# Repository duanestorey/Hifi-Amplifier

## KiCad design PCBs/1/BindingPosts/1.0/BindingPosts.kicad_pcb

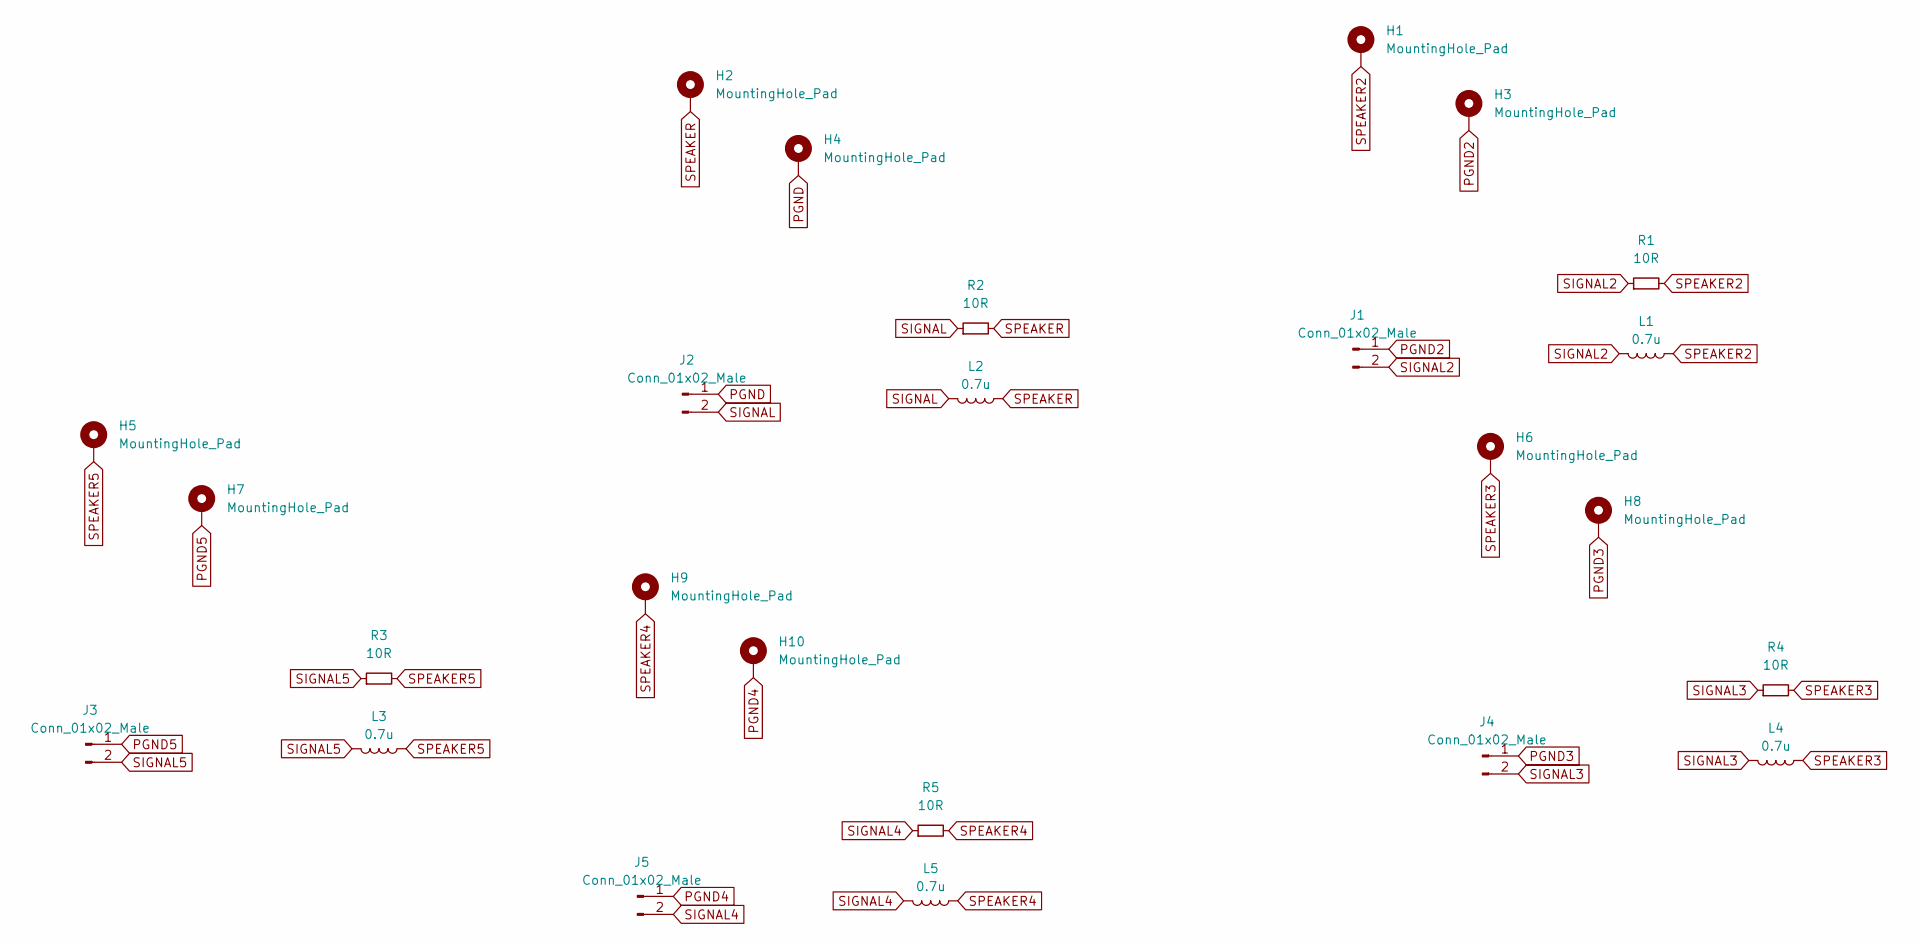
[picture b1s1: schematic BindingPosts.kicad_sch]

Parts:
H1, H2, H3, H4, H5, H6, H7, H8, H9, H10: MountingHole_Pad; MountingHole_4.3mm_M4_DIN965_Pad
J1, J2, J3, J4, J5: Conn_01x02_Male; JST_VH_B2P-VH-B_1x02_P3.96mm_Vertical
L1, L2, L3, L4, L5: 0.7u; L_Axial_L26.0mm_D10.0mm_P30.48mm_Horizontal_Fastron_77A
R1, R2, R3, R4, R5: 10R; R_Axial_Power_L25.0mm_W6.4mm_P27.94mm

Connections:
PGND: H4.1, J2.1
PGND2: H3.1, J1.1
PGND3: H8.1, J4.1
PGND4: H10.1, J5.1
PGND5: H7.1, J3.1
SIGNAL: J2.2, L2.2, R2.1
SIGNAL2: J1.2, L1.2, R1.1
SIGNAL3: J4.2, L4.2, R4.1
SIGNAL4: J5.2, L5.2, R5.1
SIGNAL5: J3.2, L3.2, R3.1
SPEAKER: H2.1, L2.1, R2.2
SPEAKER2: H1.1, L1.1, R1.2
SPEAKER3: H6.1, L4.1, R4.2
SPEAKER4: H9.1, L5.1, R5.2
SPEAKER5: H5.1, L3.1, R3.2

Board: 2 copper layers, 25 parts (0 on the bottom side), 15 nets, no tracks yet.

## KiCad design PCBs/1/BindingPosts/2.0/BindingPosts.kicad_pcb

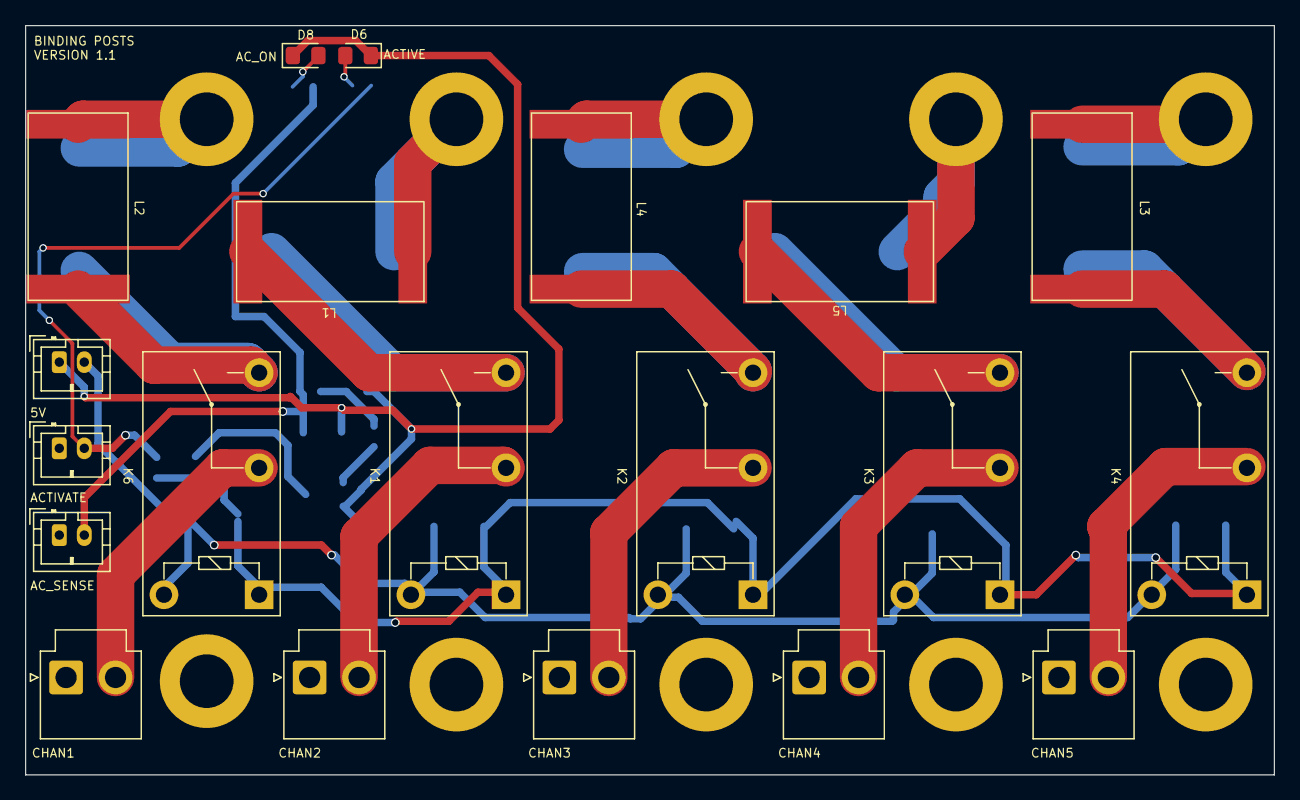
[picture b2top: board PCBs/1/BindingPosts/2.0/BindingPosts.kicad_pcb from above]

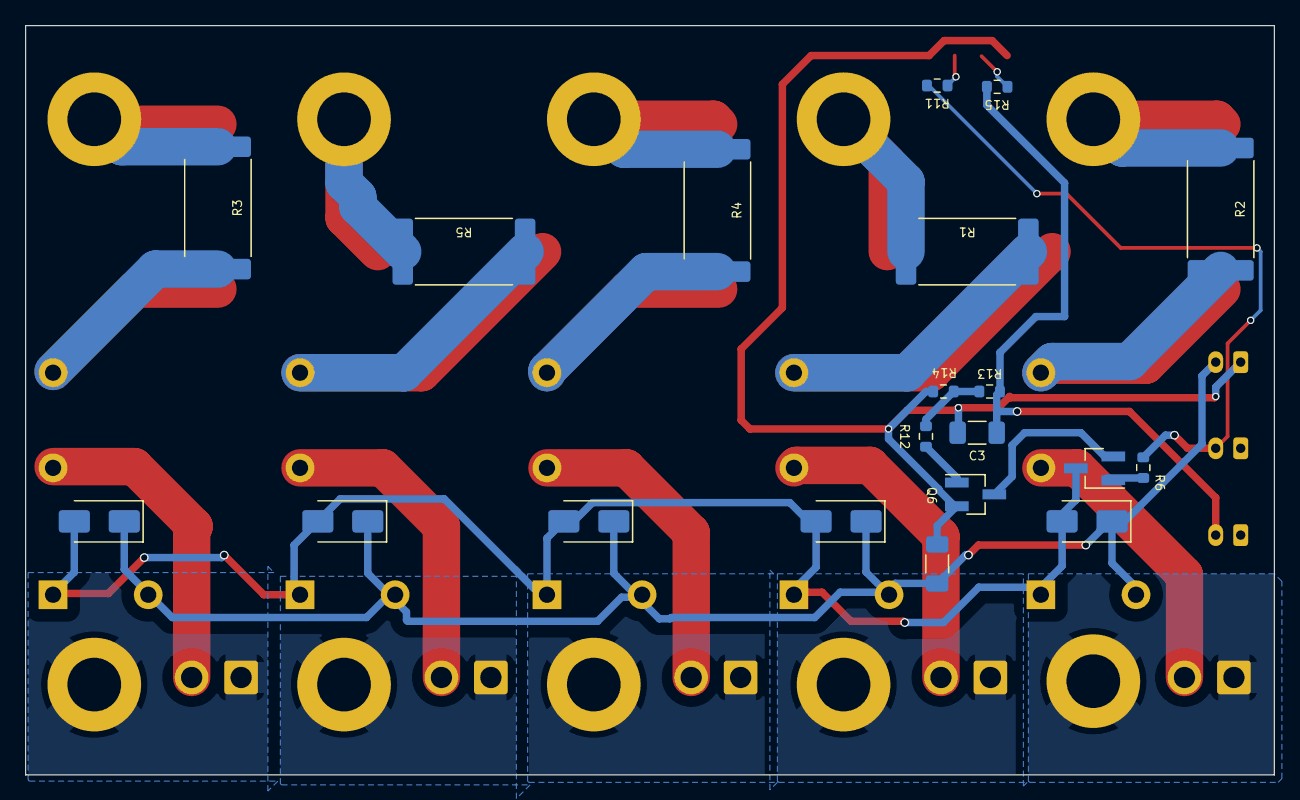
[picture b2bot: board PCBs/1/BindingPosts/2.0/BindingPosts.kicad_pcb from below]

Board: 2 copper layers, 100.0 x 60.0 mm, 50 parts (20 on the bottom side), 31 nets.

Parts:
C1: 10U; C_1206_3216Metric_Pad1.33x1.80mm_HandSolder
C3: 1U; C_1206_3216Metric_Pad1.33x1.80mm_HandSolder
D1, D2, D3, D4, D5: 1N4001; D_SMA
D6: RED; LED_0805_2012Metric_Pad1.15x1.40mm_HandSolder
D8: YELLOW; LED_0805_2012Metric_Pad1.15x1.40mm_HandSolder
H1, H2, H3, H4, H5, H6, H7, H8, H9, H10: MountingHole_Pad; MountingHole_4.3mm_M4_DIN965_Pad
J1, J2, J3, J4, J5: Conn_01x02_Male; JST_VH_B2P-VH-B_1x02_P3.96mm_Vertical
J6, J7, J8: Conn_01x02_Pin; JST_PH_B2B-PH-K_1x02_P2.00mm_Vertical
K1, K2, K3, K4, K6: G5Q-1; Relay_SPST_Omron-G5Q-1A
L1, L2, L4, L5: 0.5u; 929SQ-501JEC 500nh Air Core Inductor
L3: 538n; 929SQ-501JEC 500nh Air Core Inductor
Q1, Q6: 2SC1945; SOT-23_Handsoldering
R1, R2, R4, R5: 6.8R; R_4020_10251Metric_Pad1.65x5.30mm_HandSolder
R3: 7.5R; R_4020_10251Metric_Pad1.65x5.30mm_HandSolder
R6, R12: 820R; R_0603_1608Metric
R11: 360R; R_0603_1608Metric
R13: 20K; R_0603_1608Metric
R14: 10K; R_0603_1608Metric
R15: 430R; R_0603_1608Metric

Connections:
5V: C1.1, D1.1 (K), D2.1 (K), D3.1 (K), D4.1 (K), D5.1 (K), J6.2, K1.5, K2.5, K3.5, K4.5, K6.5
ACTIVATE: J7.2, R6.1, R11.2
AC_ACTIVE: R12.1, R13.1, R14.2
AC_SENSE: C3.1, J8.2, R13.2, R15.2
unnamed: D1.2 (A), D2.2 (A), D3.2 (A), D4.2 (A), D5.2 (A), K1.1, K2.1, K3.1, K4.1, K6.1, Q1.3 (C)
unnamed: D6.2 (A), R11.1
unnamed: D8.2 (A), R15.1
unnamed: Q1.1 (B), R6.2
unnamed: Q1.2 (E), Q6.3 (C)
unnamed: Q6.1 (B), R12.2
PGND: H4.1, J2.1
PGND2: H3.1, J1.1
PGND3: H8.1, J4.1
PGND4: H10.1, J5.1
PGND5: H7.1, J3.1
RELAY_GND: C1.2, C3.2, D6.1 (K), D8.1 (K), J6.1, Q6.2 (E), R14.1
SIGNAL1: J2.2, K6.2
SIGNAL1_OUT: K6.3, L2.2, R2.1
SIGNAL2: J1.2, K1.2
SIGNAL2_OUT: K1.3, L1.2, R1.1
SIGNAL3: J4.2, K2.2
SIGNAL3_OUT: K2.3, L4.2, R4.1
SIGNAL4: J5.2, K3.2
SIGNAL4_OUT: K3.3, L5.2, R5.1
SIGNAL5: J3.2, K4.2
SIGNAL5_OUT: K4.3, L3.2, R3.1
SPEAKER: H2.1, L2.1, R2.2
SPEAKER2: H1.1, L1.1, R1.2
SPEAKER3: H6.1, L4.1, R4.2
SPEAKER4: H9.1, L5.1, R5.2
SPEAKER5: H5.1, L3.1, R3.2

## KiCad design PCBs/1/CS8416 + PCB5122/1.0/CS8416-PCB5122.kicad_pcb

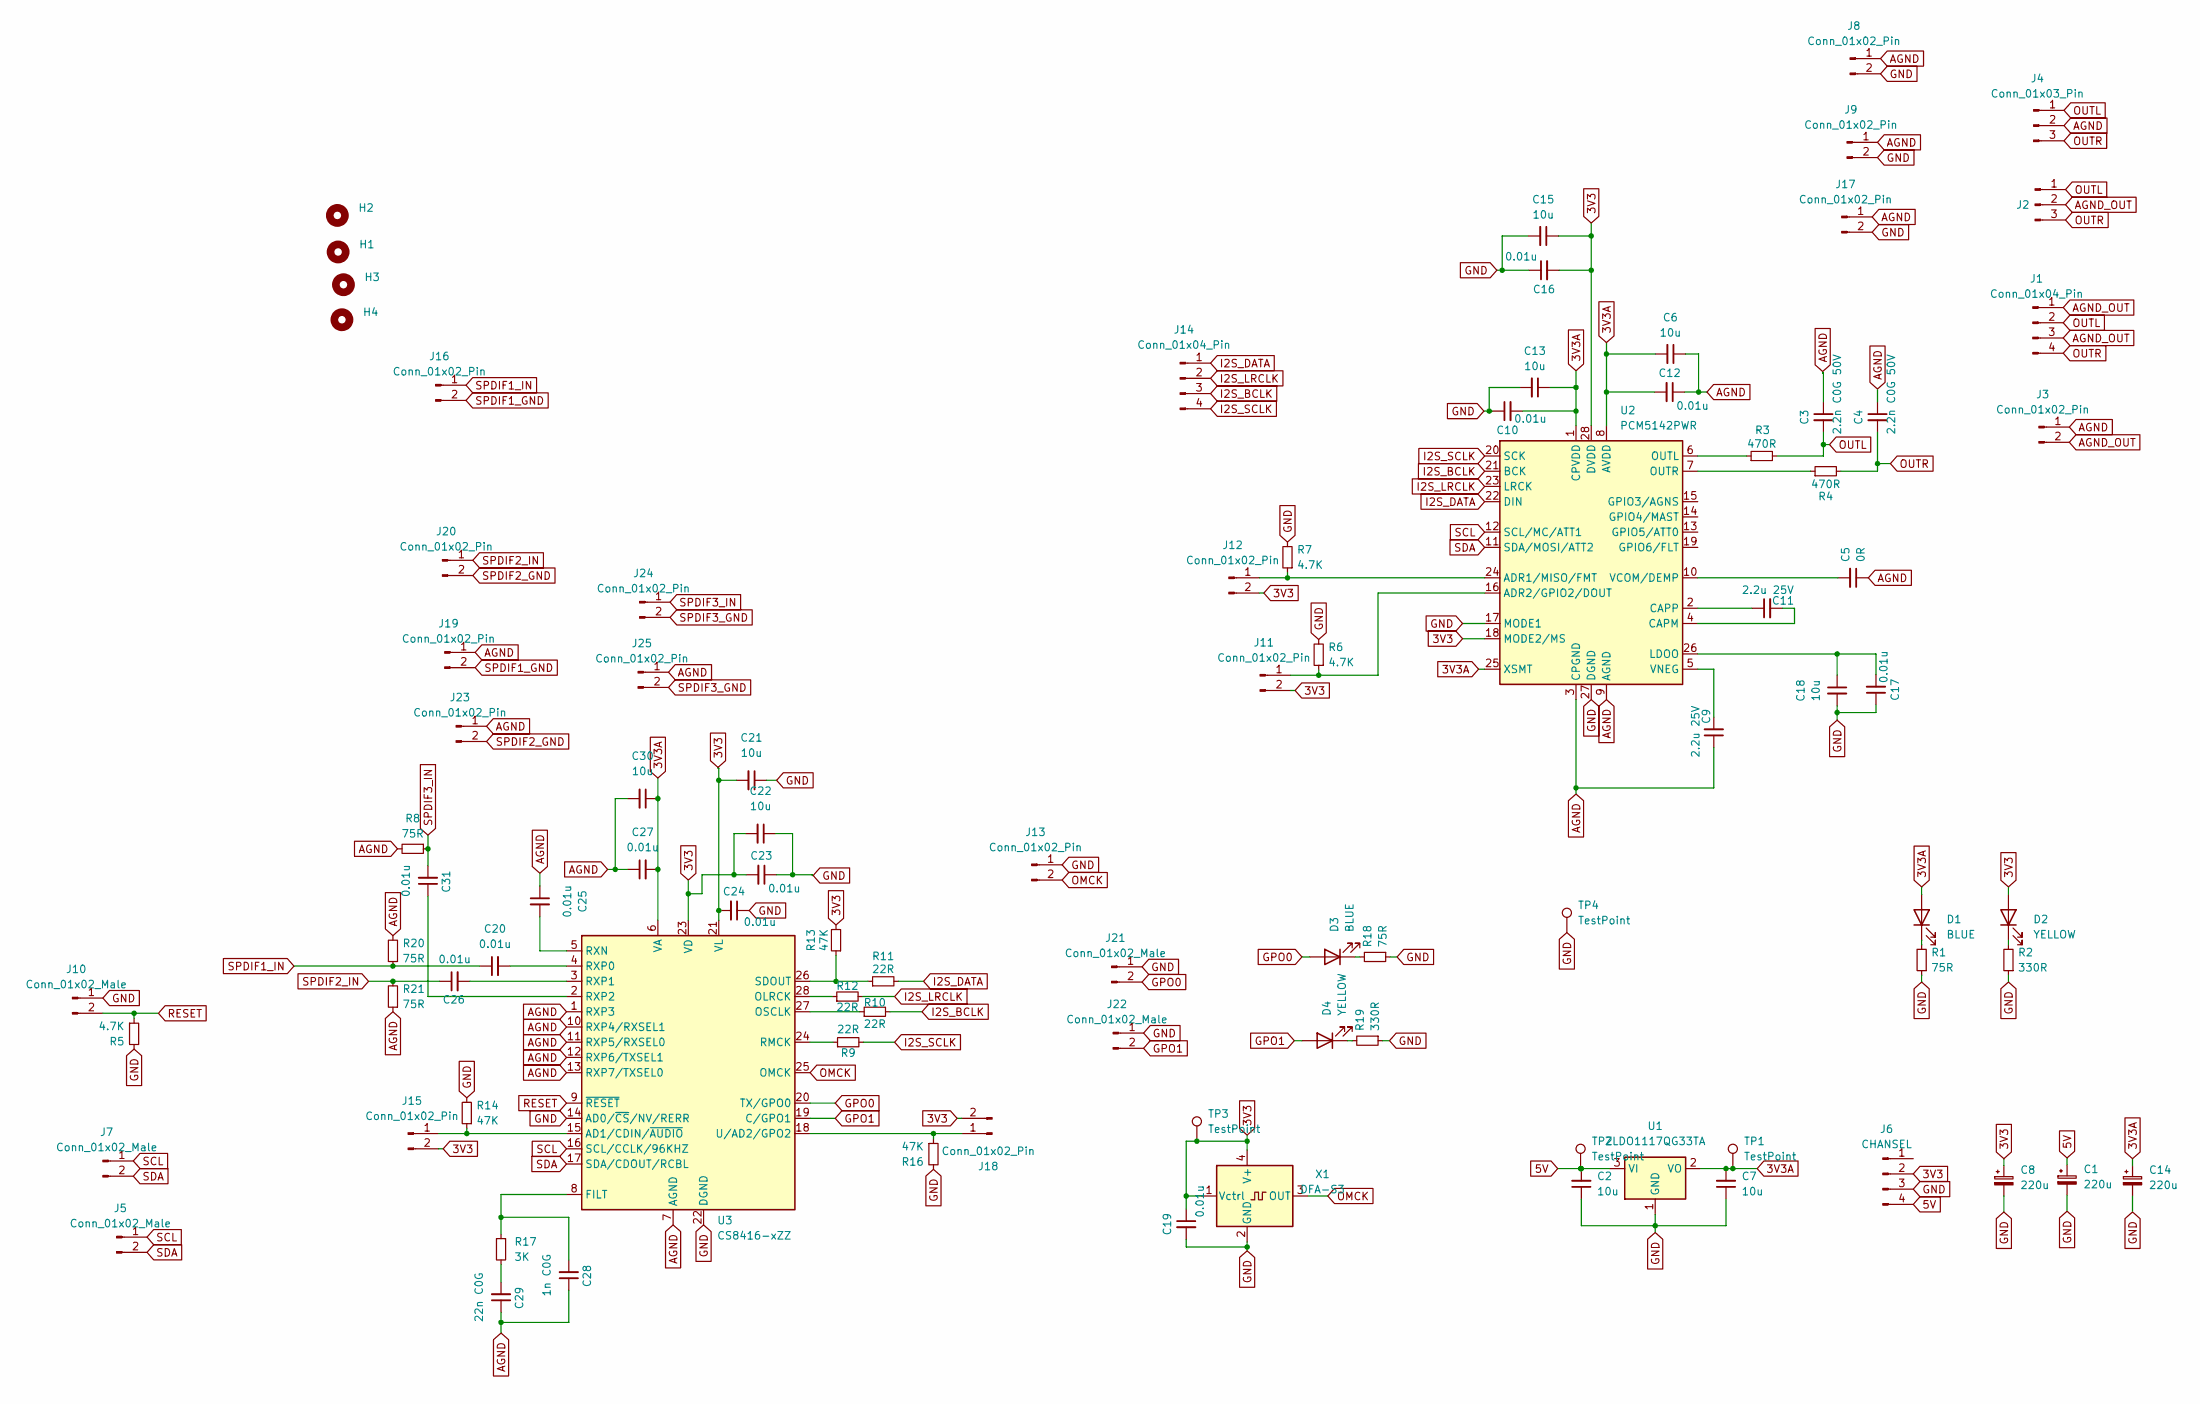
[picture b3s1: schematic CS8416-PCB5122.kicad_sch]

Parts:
C1, C8, C14: 220u; CP_Radial_D6.3mm_P2.50mm
C2, C6, C7, C13, C15, C18, C21, C22, C30: 10u; C_1206_3216Metric_Pad1.33x1.80mm_HandSolder
C3, C4: 2.2n C0G 50V; C_0805_2012Metric
C5: 0R; C_1206_3216Metric_Pad1.33x1.80mm_HandSolder
C9, C11: 2.2u 25V; C_0805_2012Metric
C10, C12, C16, C17, C19, C23, C24, C27: 0.01u; C_0805_2012Metric
C20, C25, C26, C31: 0.01u; C_0805_2012Metric_Pad1.18x1.45mm_HandSolder
C28: 1n C0G; C_0805_2012Metric_Pad1.18x1.45mm_HandSolder
C29: 22n C0G; C_0805_2012Metric_Pad1.18x1.45mm_HandSolder
D1, D3: BLUE; LED_0805_2012Metric_Pad1.15x1.40mm_HandSolder
D2, D4: YELLOW; LED_0805_2012Metric_Pad1.15x1.40mm_HandSolder
H1, H2, H3, H4: MountingHole; MountingHole_3.2mm_M3
J1: Conn_01x04_Pin; JST_PH_B4B-PH-K_1x04_P2.00mm_Vertical
J2: Conn_01x03_Pin; JST_PH_B3B-PH-K_1x03_P2.00mm_Vertical
J3, J8, J9, J11, J12, J13, J15, J17, J18, J19, J23, J25: Conn_01x02_Pin; PinHeader_1x02_P2.54mm_Vertical
J4: Conn_01x03_Pin; PinHeader_1x03_P2.54mm_Vertical
J5, J7, J10, J21, J22: Conn_01x02_Male; JST_PH_B2B-PH-K_1x02_P2.00mm_Vertical
J6: CHANSEL; JST_XH_B4B-XH-A_1x04_P2.50mm_Vertical
J14: Conn_01x04_Pin; PinHeader_1x04_P2.54mm_Vertical
J16, J20, J24: Conn_01x02_Pin; JST_XH_B2B-XH-A_1x02_P2.50mm_Vertical
R1, R8, R18, R20, R21: 75R; R_0603_1608Metric_Pad0.98x0.95mm_HandSolder
R2, R19: 330R; R_0603_1608Metric_Pad0.98x0.95mm_HandSolder
R3, R4: 470R; R_0603_1608Metric_Pad0.98x0.95mm_HandSolder
R5, R6, R7: 4.7K; R_0603_1608Metric_Pad0.98x0.95mm_HandSolder
R9, R10, R11, R12: 22R; R_0603_1608Metric_Pad0.98x0.95mm_HandSolder
R13, R14, R16: 47K; R_0603_1608Metric_Pad0.98x0.95mm_HandSolder
R17: 3K; R_0603_1608Metric_Pad0.98x0.95mm_HandSolder
TP1, TP2, TP3, TP4: TestPoint; TestPoint_Pad_2.0x2.0mm
U1: ZLDO1117QG33TA; SOT-223-3_TabPin2
U2: PCM5142PWR; TSSOP-28_4.4x9.7mm_P0.65mm
U3: CS8416-xZZ; TSSOP-28_4.4x9.7mm_P0.65mm
X1: DFA-S3; Oscillator_SMD_EuroQuartz_XO53-4Pin_5.0x3.2mm

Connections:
3V3: C8.1, C15.1, C16.2, C19.1, C21.2, C22.2, C23.2, C24.2, D2.2 (A), J6.2, J11.2, J12.2, J15.2, J18.2, R13.2, TP3.1, U2.18 (MODE2/MS), U2.28 (DVDD), U3.21 (VL), U3.23 (VD), X1.1 (Vctrl), X1.4 (V+)
3V3A: C6.2, C7.2, C10.2, C12.2, C13.1, C14.1, C27.2, C30.1, D1.2 (A), TP1.1, U1.2 (VO), U2.1 (CPVDD), U2.8 (AVDD), U2.25 (XSMT), U3.6 (VA)
5V: C1.1, C2.2, J6.4, TP2.1, U1.3 (VI)
AGND: C3.1, C4.1, C5.1, C6.1, C9.1, C12.1, C25.1, C27.1, C28.1, C29.1, C30.2, J3.1, J4.2, J8.1, J9.1, J17.1, J19.1, J23.1, J25.1, R8.2, R20.2, R21.1, U2.3 (CPGND), U2.9 (AGND), U3.1 (RXP3), U3.7 (AGND), U3.10 (RXP4/RXSEL1), U3.11 (RXP5/RXSEL0), U3.12 (RXP6/TXSEL1), U3.13 (RXP7/TXSEL0)
AGND_OUT: J1.1, J1.3, J2.2, J3.2
GND: C1.2, C2.1, C7.1, C8.2, C10.1, C13.2, C14.2, C15.2, C16.1, C17.1, C18.2, C19.2, C21.1, C22.1, C23.1, C24.1, J6.3, J8.2, J9.2, J10.1, J13.1, J17.2, J21.1, J22.1, R1.1, R2.1, R5.2, R6.2, R7.2, R14.2, R16.2, R18.1, R19.1, TP4.1, U1.1 (GND), U2.17 (MODE1), U2.27 (DGND), U3.14 (AD0/~CS/NV/RERR), U3.22 (DGND), X1.2 (GND)
GPO0: D3.2 (A), J21.2, U3.20 (TX/GPO0)
GPO1: D4.2 (A), J22.2, U3.19 (C/GPO1)
I2S_BCLK: J14.3, R10.2, U2.21 (BCK)
I2S_DATA: J14.1, R11.2, U2.22 (DIN)
I2S_LRCLK: J14.2, R12.2, U2.23 (LRCK)
I2S_SCLK: J14.4, R9.2, U2.20 (SCK)
unnamed: C29.2, R17.2
unnamed: D1.1 (K), R1.2
unnamed: D2.1 (K), R2.2
unnamed: D3.1 (K), R18.2
unnamed: D4.1 (K), R19.2
unnamed: J11.1, R6.1, U2.16 (ADR2/GPIO2/DOUT)
unnamed: J12.1, R7.1, U2.24 (ADR1/MISO/FMT)
unnamed: J15.1, R14.1, U3.15 (AD1/CDIN/~AUDIO)
unnamed: J18.1, R16.1, U3.18 (U/AD2/GPO2)
unnamed: C11.2, U2.4 (CAPM)
unnamed: C11.1, U2.2 (CAPP)
unnamed: C17.2, C18.1, U2.26 (LDOO)
unnamed: R3.1, U2.6 (OUTL)
unnamed: R4.1, U2.7 (OUTR)
unnamed: C5.2, U2.10 (VCOM/DEMP)
unnamed: C9.2, U2.5 (VNEG)
unnamed: C28.2, R17.1, U3.8 (FILT)
unnamed: R12.1, U3.28 (OLRCK)
unnamed: R10.1, U3.27 (OSCLK)
unnamed: R9.1, U3.24 (RMCK)
unnamed: C25.2, U3.5 (RXN)
unnamed: C20.2, U3.4 (RXP0)
unnamed: C26.2, U3.3 (RXP1)
unnamed: C31.1, U3.2 (RXP2)
unnamed: R11.1, R13.1, U3.26 (SDOUT)
OMCK: J13.2, U3.25 (OMCK), X1.3 (OUT)
OUTL: C3.2, J1.2, J2.1, J4.1, R3.2
OUTR: C4.2, J1.4, J2.3, J4.3, R4.2
RESET: J10.2, R5.1, U3.9 (~RESET)
SCL: J5.1, J7.1, U2.12 (SCL/MC/ATT1), U3.16 (SCL/CCLK/96KHZ)
SDA: J5.2, J7.2, U2.11 (SDA/MOSI/ATT2), U3.17 (SDA/CDOUT/RCBL)
SPDIF1_GND: J16.2, J19.2
SPDIF1_IN: C20.1, J16.1, R20.1
SPDIF2_GND: J20.2, J23.2
SPDIF2_IN: C26.1, J20.1, R21.2
SPDIF3_GND: J24.2, J25.2
SPDIF3_IN: C31.2, J24.1, R8.1

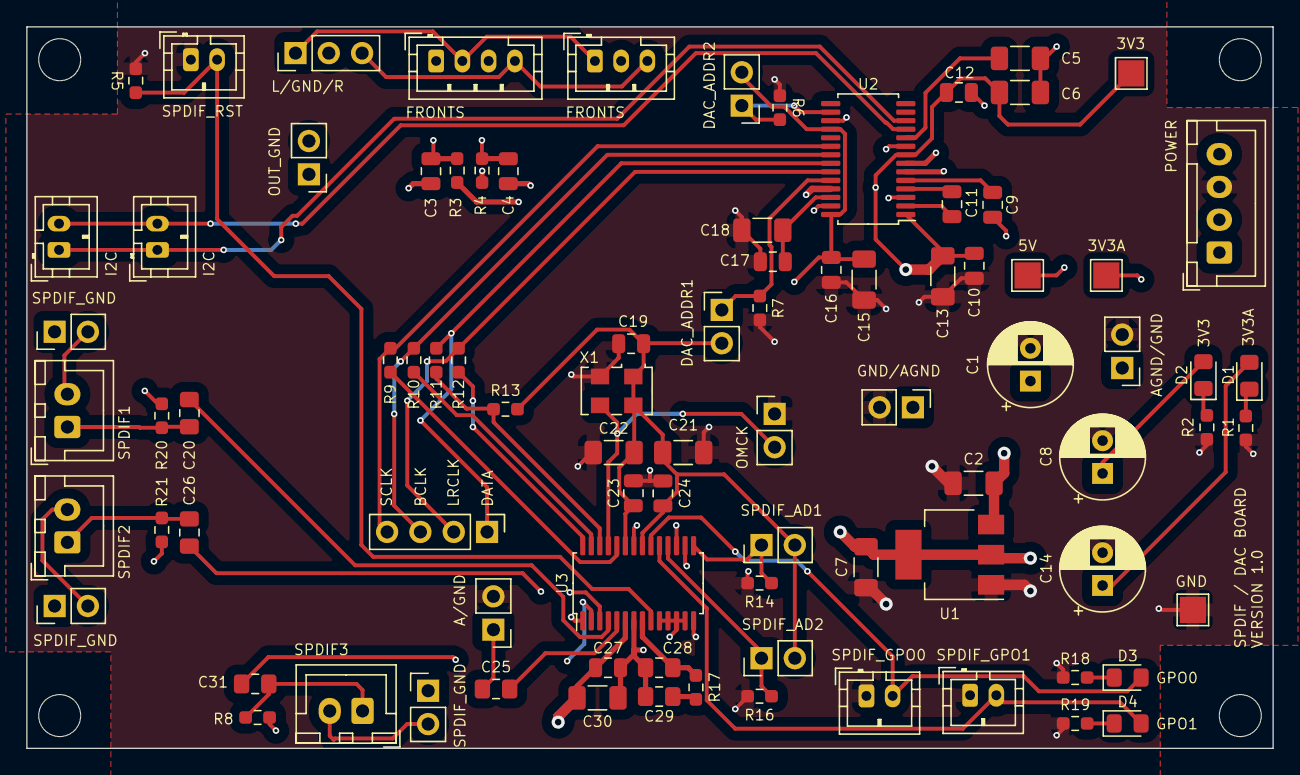
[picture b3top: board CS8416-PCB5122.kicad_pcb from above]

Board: 4 copper layers, 95.0 x 55.0 mm, 92 parts (0 on the bottom side), 49 nets.

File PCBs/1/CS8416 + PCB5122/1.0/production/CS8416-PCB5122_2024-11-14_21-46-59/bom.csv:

Designator,Footprint,Quantity,Value,LCSC Part #
"C1, C14, C8",CP_Radial_D6.3mm_P2.50mm,3,220u,
"C10, C12, C16, C17, C19, C20, C23, C24, C25, C26, C27",0805,11,0.01u,
"C11, C9",0805,2,2.2u 25V,
"C13, C15, C18, C2, C21, C22, C30, C5, C6, C7",1206,10,10u,
C28,0805,1,1n C0G,
C29,0805,1,22n C0G,
"C3, C4",0805,2,2.2n C0G 50V,
"D1, D3",0805,2,BLUE,
"D2, D4",0805,2,YELLOW,
"H1, H2, H3, H4",MountingHole_3.2mm_M3,4,MountingHole,
J1,JST_PH_B4B-PH-K_1x04_P2.00mm_Vertical,1,Conn_01x04_Pin,
"J10, J21, J22, J5, J7",JST_PH_B2B-PH-K_1x02_P2.00mm_Vertical,5,Conn_01x02_Male,
"J11, J12, J13, J15, J17, J18, J19, J23, J3, J8, J9",PinHeader_1x02_P2.54mm_Vertical,11,Conn_01x02_Pin,
J14,PinHeader_1x04_P2.54mm_Vertical,1,Conn_01x04_Pin,
"J16, J20",JST_XH_B2B-XH-A_1x02_P2.50mm_Vertical,2,Conn_01x02_Pin,
J2,JST_PH_B3B-PH-K_1x03_P2.00mm_Vertical,1,Conn_01x03_Pin,
J4,PinHeader_1x03_P2.54mm_Vertical,1,Conn_01x03_Pin,
J6,JST_XH_B4B-XH-A_1x04_P2.50mm_Vertical,1,CHANSEL,
"R1, R15, R18, R8",0603,4,75R,
"R10, R11, R12, R9",0603,4,22R,
"R13, R14, R16",0603,3,47K,
R17,0603,1,3K,
"R19, R2",0603,2,330R,
"R3, R4",0603,2,470R,
"R5, R6, R7",0603,3,4.7K,
"T1, T2",DA101C,2,DA101C,
U1,SOT-223-3_TabPin2,1,AMS1117-3.3,
U2,TSSOP-28_4.4x9.7mm_P0.65mm,1,PCM5142PWR,
U3,TSSOP-28-1EP_4.4x9.7mm_P0.65mm,1,CS8416-xZZ,
X1,Oscillator_SMD_EuroQuartz_XO53-4Pin_5.0x3.2mm,1,DFA-S3,

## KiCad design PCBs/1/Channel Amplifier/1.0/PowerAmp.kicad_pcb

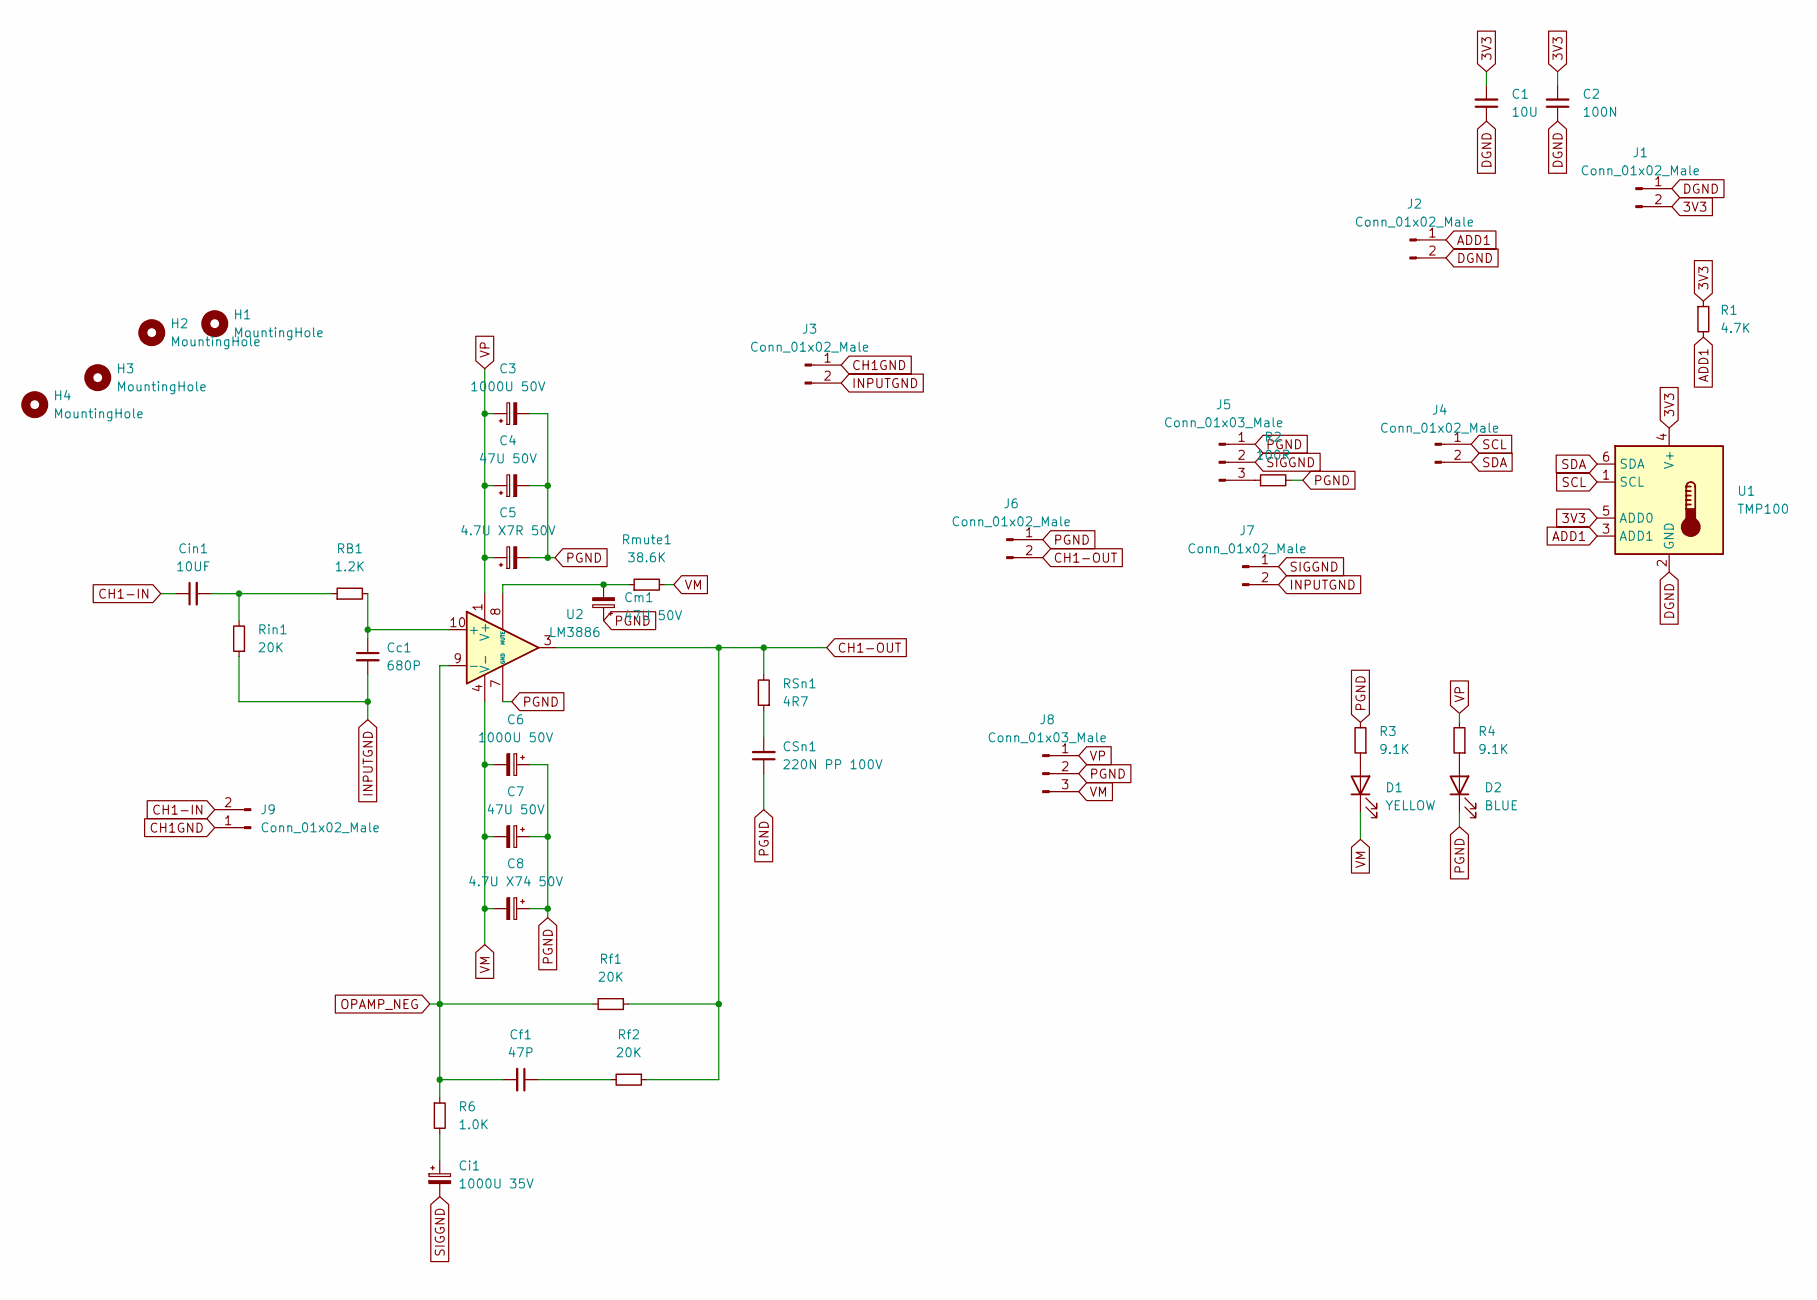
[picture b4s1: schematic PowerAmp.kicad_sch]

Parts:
C1: 10U; R_1206_3216Metric_Pad1.30x1.75mm_HandSolder
C2: 100N; R_0805_2012Metric_Pad1.20x1.40mm_HandSolder
C3, C6: 1000U 50V; CP_Radial_D12.5mm_P5.00mm
C4, C7: 47U 50V; CP_Radial_D6.3mm_P2.50mm
C5: 4.7U X7R 50V; C_Disc_D6.0mm_W4.4mm_P5.00mm
C8: 4.7U X74 50V; C_Disc_D6.0mm_W4.4mm_P5.00mm
CSn1: 220N PP 100V; C_Rect_L18.0mm_W7.0mm_P15.00mm_FKS3_FKP3
Cc1: 680P; C_Disc_D11.0mm_W5.0mm_P10.00mm
Cf1: 47P; C_Disc_D9.0mm_W5.0mm_P7.50mm
Ci1: 1000U 35V; CP_Radial_D16.0mm_P7.50mm
Cin1: 10UF; CP_Radial_D5.0mm_P2.00mm
Cm1: 47U 50V; CP_Radial_D6.3mm_P2.50mm
D1: YELLOW; LED_0805_2012Metric_Pad1.15x1.40mm_HandSolder
D2: BLUE; LED_0805_2012Metric_Pad1.15x1.40mm_HandSolder
H1, H2, H3, H4: MountingHole; MountingHole_3mm
J1, J4, J9: Conn_01x02_Male; JST_PH_B2B-PH-K_1x02_P2.00mm_Vertical
J2, J3, J7: Conn_01x02_Male; PinHeader_1x02_P2.54mm_Vertical
J5: Conn_01x03_Male; PinHeader_1x03_P2.54mm_Vertical
J6: Conn_01x02_Male; JST_VH_B2P-VH_1x02_P3.96mm_Vertical
J8: Conn_01x03_Male; JST_VH_B3P-VH-B_1x03_P3.96mm_Vertical
R1: 4.7K; R_0603_1608Metric_Pad0.98x0.95mm_HandSolder
R2: 100R; R_0805_2012Metric_Pad1.20x1.40mm_HandSolder
R3, R4: 9.1K; R_0805_2012Metric_Pad1.20x1.40mm_HandSolder
R6: 1.0K; R_Axial_DIN0207_L6.3mm_D2.5mm_P10.16mm_Horizontal
RB1: 1.2K; R_Axial_DIN0207_L6.3mm_D2.5mm_P10.16mm_Horizontal
RSn1: 4R7; R_Axial_DIN0411_L9.9mm_D3.6mm_P12.70mm_Horizontal
Rf1, Rf2: 20K; R_Axial_DIN0207_L6.3mm_D2.5mm_P10.16mm_Horizontal
Rin1: 20K; R_Axial_DIN0207_L6.3mm_D2.5mm_P10.16mm_Horizontal
Rmute1: 38.6K; R_Axial_DIN0207_L6.3mm_D2.5mm_P10.16mm_Horizontal
U1: TMP100; SOT-23-6
U2: LM3886; TO-220-11_P3.4x5.08mm_StaggerOdd_Lead4.85mm_Vertical

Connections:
3V3: C1.2, C2.2, J1.2, R1.1, U1.4 (V+), U1.5 (ADD0)
ADD1: J2.1, R1.2, U1.3 (ADD1)
CH1-IN: Cin1.1, J9.2
CH1-OUT: J6.2, RSn1.2, Rf1.1, Rf2.1, U2.3
CH1GND: J3.1, J9.1
DGND: C1.1, C2.1, J1.1, J2.2, U1.2 (GND)
INPUTGND: Cc1.2, J3.2, J7.2, Rin1.1
unnamed: CSn1.2, RSn1.1
unnamed: Cf1.1, Rf2.2
unnamed: Ci1.1, R6.2
unnamed: Cin1.2, RB1.1, Rin1.2
unnamed: D1.2 (A), R3.1
unnamed: D2.2 (A), R4.1
unnamed: J5.3, R2.1
unnamed: Cc1.1, RB1.2, U2.10 (+)
unnamed: Cm1.2, Rmute1.1, U2.8 (MUTE)
OPAMP_NEG: Cf1.2, R6.1, Rf1.2, U2.9 (-)
PGND: C3.2, C4.2, C5.2, C6.1, C7.1, C8.1, CSn1.1, Cm1.1, D2.1 (K), J5.1, J6.1, J8.2, R2.2, R3.2, U2.7 (GND)
SCL: J4.1, U1.1 (SCL)
SDA: J4.2, U1.6 (SDA)
SIGGND: Ci1.2, J5.2, J7.1
VM: C6.2, C7.2, C8.2, D1.1 (K), J8.3, Rmute1.2, U2.4 (V-)
VP: C3.1, C4.1, C5.1, J8.1, R4.2, U2.1 (V+), U2.5 (V+)

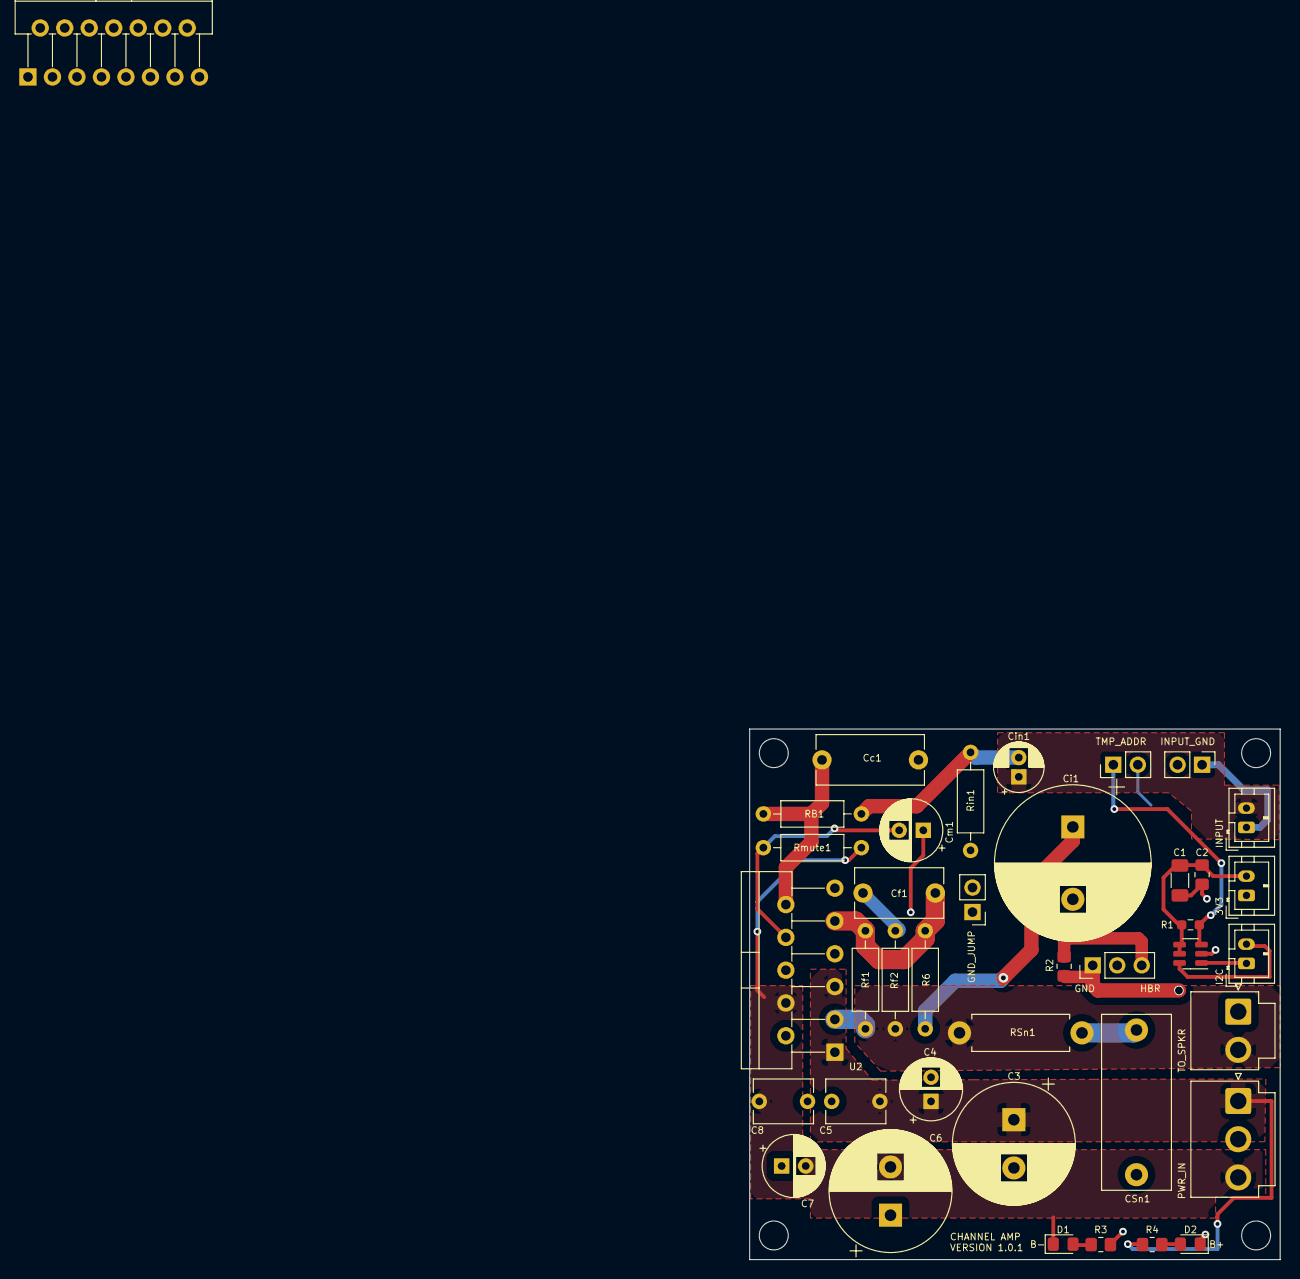
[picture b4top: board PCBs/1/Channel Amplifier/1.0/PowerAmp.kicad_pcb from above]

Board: 2 copper layers, 55.0 x 55.0 mm, 43 parts (0 on the bottom side), 23 nets.

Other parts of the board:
U3: LM4766; TO-220-15_P2.54x2.54mm_StaggerOdd_Lead4.58mm_Vertical

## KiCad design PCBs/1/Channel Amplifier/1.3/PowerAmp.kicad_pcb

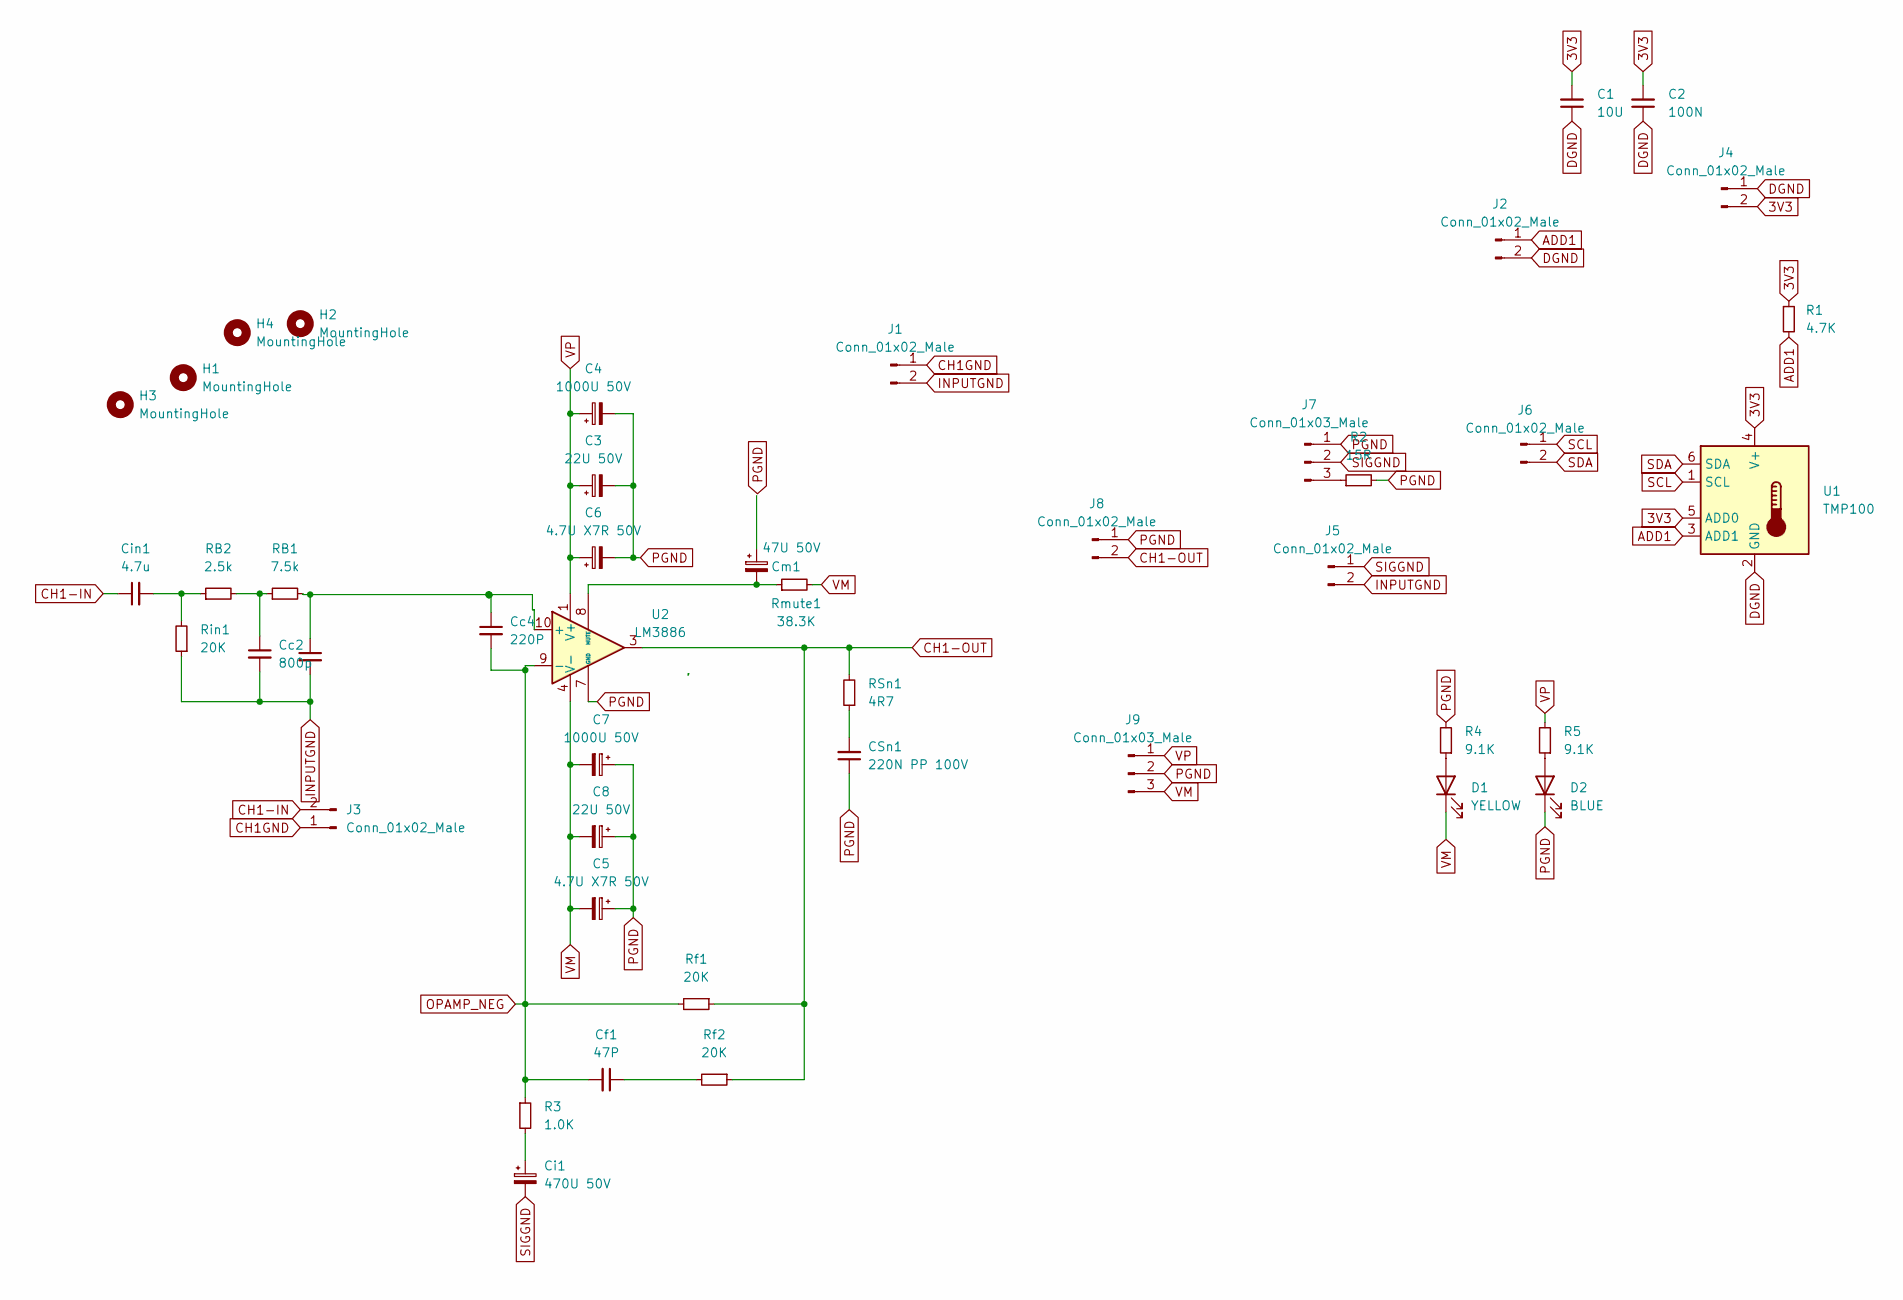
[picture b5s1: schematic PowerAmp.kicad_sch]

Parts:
C1: 10U; R_1206_3216Metric_Pad1.30x1.75mm_HandSolder
C2: 100N; R_0805_2012Metric_Pad1.20x1.40mm_HandSolder
C3, C8: 22U 50V; CP_Radial_D6.3mm_P2.50mm
C4, C7: 1000U 50V; CP_Radial_D12.5mm_P5.00mm
C5, C6: 4.7U X7R 50V; C_1206_3216Metric_Pad1.33x1.80mm_HandSolder
CSn1: 220N PP 100V; C_Rect_L18.0mm_W7.0mm_P15.00mm_FKS3_FKP3
Cc1: 68p; C_1206_3216Metric_Pad1.33x1.80mm_HandSolder
Cc2: 800p; C_1206_3216Metric_Pad1.33x1.80mm_HandSolder
Cc4: 220P; C_1206_3216Metric_Pad1.33x1.80mm_HandSolder
Cf1: 47P; C_1206_3216Metric_Pad1.33x1.80mm_HandSolder
Ci1: 470U 50V; CP_Radial_D12.5mm_P5.00mm
Cin1: 4.7u; CP_Radial_D5.0mm_P2.00mm
Cm1: 47U 50V; CP_Radial_D6.3mm_P2.50mm
D1: YELLOW; LED_0805_2012Metric_Pad1.15x1.40mm_HandSolder
D2: BLUE; LED_0805_2012Metric_Pad1.15x1.40mm_HandSolder
H1, H2, H3, H4: MountingHole; MountingHole_3mm
J1, J2, J5: Conn_01x02_Male; PinHeader_1x02_P2.54mm_Vertical
J3, J4, J6: Conn_01x02_Male; JST_PH_B2B-PH-K_1x02_P2.00mm_Vertical
J7: Conn_01x03_Male; PinHeader_1x03_P2.54mm_Vertical
J8: Conn_01x02_Male; JST_VH_B2P-VH_1x02_P3.96mm_Vertical
J9: Conn_01x03_Male; JST_VH_B3P-VH-B_1x03_P3.96mm_Vertical
R1: 4.7K; R_0603_1608Metric_Pad0.98x0.95mm_HandSolder
R2: 15R; R_0805_2012Metric_Pad1.20x1.40mm_HandSolder
R3: 1.0K; R_1206_3216Metric_Pad1.30x1.75mm_HandSolder
R4, R5: 9.1K; R_0805_2012Metric_Pad1.20x1.40mm_HandSolder
RB1: 7.5k; R_1206_3216Metric_Pad1.30x1.75mm_HandSolder
RB2: 2.5k; R_1206_3216Metric_Pad1.30x1.75mm_HandSolder
RSn1: 4R7; R_Axial_DIN0411_L9.9mm_D3.6mm_P12.70mm_Horizontal
Rf1, Rf2: 20K; R_1206_3216Metric_Pad1.30x1.75mm_HandSolder
Rin1: 20K; R_1206_3216Metric_Pad1.30x1.75mm_HandSolder
Rmute1: 38.3K; R_1206_3216Metric_Pad1.30x1.75mm_HandSolder
U1: TMP100; SOT-23-6
U2: LM3886; TO-220-11_P3.4x5.08mm_StaggerOdd_Lead4.85mm_Vertical

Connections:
3V3: C1.2, C2.2, J4.2, R1.1, U1.4 (V+), U1.5 (ADD0)
ADD1: J2.1, R1.2, U1.3 (ADD1)
CH1-IN: Cin1.1, J3.2
CH1-OUT: J8.2, RSn1.2, Rf1.1, Rf2.1, U2.3
CH1GND: J1.1, J3.1
DGND: C1.1, C2.1, J2.2, J4.1, U1.2 (GND)
INPUTGND: Cc1.2, Cc2.2, J1.2, J5.2, Rin1.1
unnamed: CSn1.2, RSn1.1
unnamed: Cc2.1, RB1.1, RB2.2
unnamed: Cf1.1, Rf2.2
unnamed: Ci1.1, R3.2
unnamed: Cin1.2, RB2.1, Rin1.2
unnamed: D1.2 (A), R4.1
unnamed: D2.2 (A), R5.1
unnamed: J7.3, R2.1
unnamed: Cc1.1, Cc4.1, RB1.2, U2.10 (+)
unnamed: Cm1.2, Rmute1.1, U2.8 (MUTE)
OPAMP_NEG: Cc4.2, Cf1.2, R3.1, Rf1.2, U2.9 (-)
PGND: C3.2, C4.2, C5.1, C6.2, C7.1, C8.1, CSn1.1, D2.1 (K), J7.1, J8.1, J9.2, R2.2, R4.2, U2.7 (GND)
SCL: J6.1, U1.1 (SCL)
SDA: J6.2, U1.6 (SDA)
SIGGND: Ci1.2, J5.1, J7.2
VM: C5.2, C7.2, C8.2, D1.1 (K), J9.3, Rmute1.2, U2.4 (V-)
VP: C3.1, C4.1, C6.1, J9.1, R5.2, U2.1 (V+), U2.5 (V+)
